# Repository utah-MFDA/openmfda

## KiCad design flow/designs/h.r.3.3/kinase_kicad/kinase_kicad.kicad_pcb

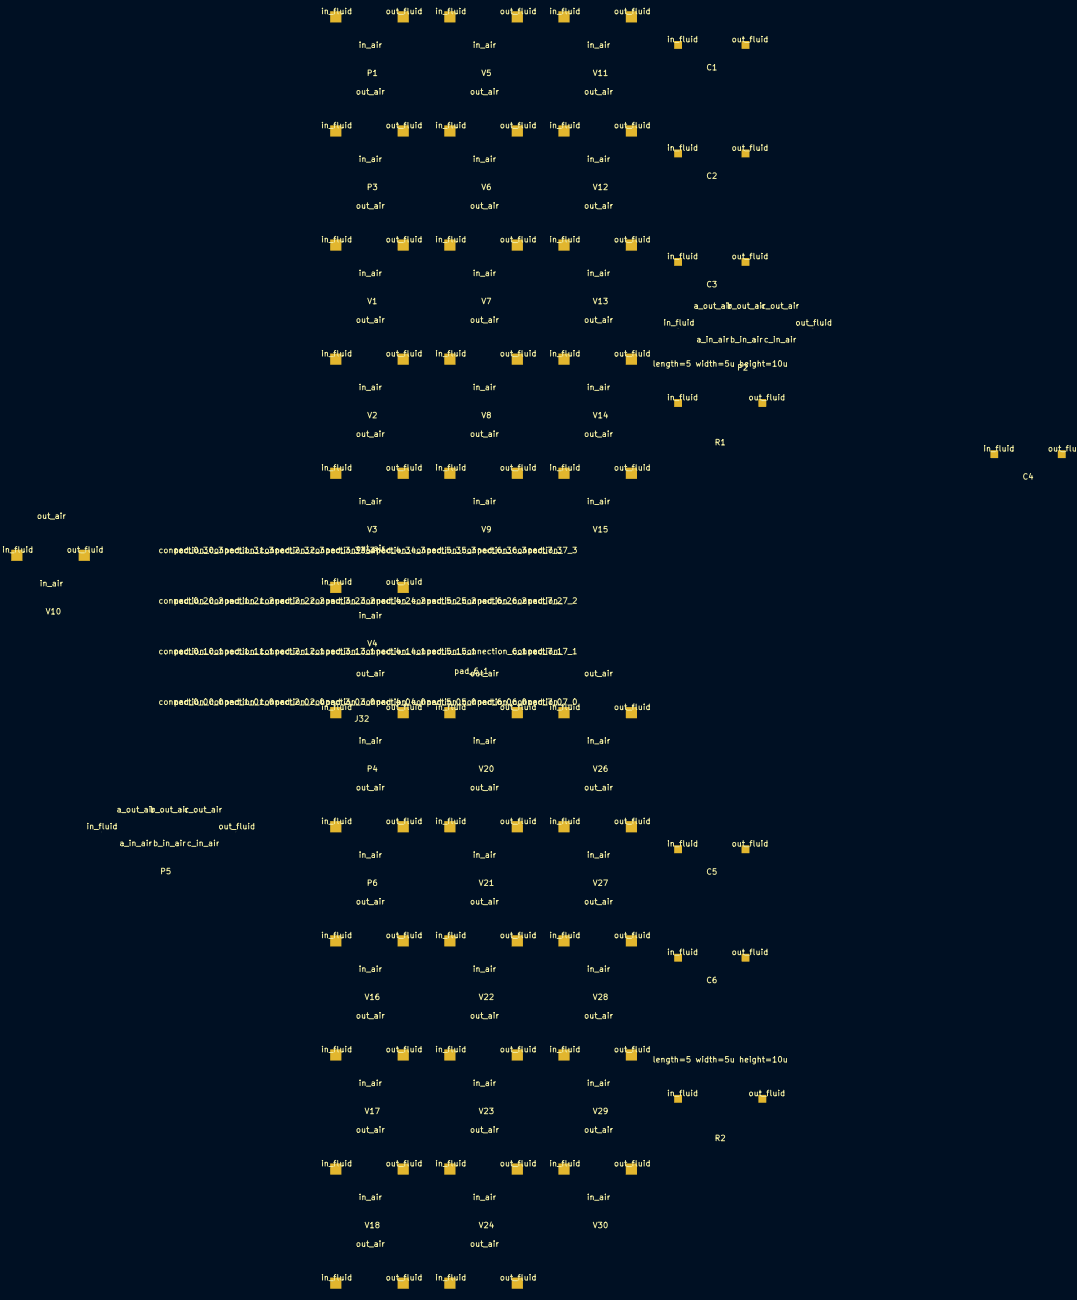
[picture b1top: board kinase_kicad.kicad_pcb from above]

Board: 10 copper layers, 54 parts (0 on the bottom side), 52 nets.

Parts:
C1, C2, C3, C4, C5, C6: serpentine_100px_0
J1, J2, J3, J4, J27, J28, J29, J30, J31: pinhole_325px_0
J32: interconnect_8x4
P1, P3, P4, P6: valve_80px_1
P2, P5: pump_40px_0
R1, R2: length=5 width=5u height=10u; inline_res_40nl
V1, V2, V3, V4, V5, V6, V7, V8, V9, V10, V11, V12, V13, V14, V15, V16, V17, V18, V19, V20, V21, V22, V23, V24, V25, V26, V27, V28, V29, V30: valve_80px_1

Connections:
/component1/fluid_in3: J4.1 (connect_1), V22.3 (c)
/component1/out: J31.1 (connect_1), V30.2 (fluid_right)
/component/control.circulate1: J32.14, V4.3 (control_in)
/component/control.circulate2: J32.10, V2.3 (control_in)
/component/control.circulate3: J32.11, V3.3 (control_in)
/component/control.circulate_in: J32.9, V1.3 (control_in)
/component/control.circulate_out: J32.16, V5.3 (control_in)
/component/control.filter1: J32.12, V8.3 (control)
/component/control.filter2: J32.13, V9.3 (control)
/component/control.filter3: J32.24, V11.3 (control)
/component/control.filter4: J32.23, V10.3 (control)
/component/control.flush1: J32.15, V6.3 (control_in)
/component/control.flush2: J32.17, V12.3 (control_in)
/component/control.flush3: J32.19, V14.3 (control_in)
/component/control.out: J32.22, V15.3 (control_in)
/component/control.stage: J32.18, V13.3 (control_in)
/component/fluid_in1: J1.1 (connect_1), V7.1 (a), V22.1 (a)
/component/fluid_in2: J2.1 (connect_1), V7.2 (b), V22.2 (b)
/component/fluid_in3: J3.1 (connect_1), V7.3 (c)
/component/flush_1: J28.1 (connect_1), V6.2 (fluid_right), V21.2 (fluid_right)
/component/flush_2: J29.1 (connect_1), V12.2 (fluid_right), V27.2 (fluid_right)
/component/flush_3: J30.1 (connect_1), V14.1 (fluid_left), V29.1 (fluid_left)
/component/out: J27.1 (connect_1), V15.2 (fluid_right)
/component/pump1: J32.1, P2.3 (pump_1)
/component/pump2: J32.2, P2.5 (pump_2)
/component/pump3: J32.3, P2.7 (pump_3)
/pump_flush_lh_1: P2.4 (pump_1f), P5.3 (pump_1)
/pump_flush_lh_2: P2.6 (pump_2fl), P5.5 (pump_2)
unnamed: C1.1 (in_1), V2.1 (fluid_left)
unnamed: C2.1 (in_1), V4.1 (fluid_left), V6.1 (fluid_left)
unnamed: C3.1 (in_1), V11.2 (fluid_out)
unnamed: C4.1 (in_1), V17.1 (fluid_left)
unnamed: C5.1 (in_1), V19.1 (fluid_left), V21.1 (fluid_left)
unnamed: C6.1 (in_1), V26.2 (fluid_out)
unnamed: P1.1 (in), V8.2 (fluid_out)
unnamed: P3.1 (in), R1.1 (in_1)
unnamed: P3.2 (out), V9.1 (fluid_in)
unnamed: P4.1 (in), V23.2 (fluid_out)
unnamed: P6.1 (in), R2.1 (in_1)
unnamed: P6.2 (out), V24.1 (fluid_in)
unnamed: V1.1 (fluid_left), V2.2 (fluid_right), V3.1 (fluid_left)
unnamed: V3.2 (fluid_right), V8.1 (fluid_in)
unnamed: V4.2 (fluid_right), V5.2 (fluid_right), V9.2 (fluid_out)
unnamed: V10.2 (fluid_out), V13.2 (fluid_right)
unnamed: V11.1 (fluid_in), V14.2 (fluid_right), V15.1 (fluid_left)
unnamed: V5.1 (fluid_left), V12.1 (fluid_left), V13.1 (fluid_left)
unnamed: V16.1 (fluid_left), V17.2 (fluid_right), V18.1 (fluid_left)
unnamed: V18.2 (fluid_right), V23.1 (fluid_in)
unnamed: V19.2 (fluid_right), V20.2 (fluid_right), V24.2 (fluid_out)
unnamed: V20.1 (fluid_left), V27.1 (fluid_left), V28.1 (fluid_left)
unnamed: V25.2 (fluid_out), V28.2 (fluid_right)
unnamed: V26.1 (fluid_in), V29.2 (fluid_right), V30.1 (fluid_left)

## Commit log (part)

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2023-12-05 Add dockerfile.
2023-12-06 Update docker file to use ubuntu
2023-12-11 Fixes to dockerfile, tcl and python scripts to get running with docker.
2023-12-12 Demo now working with latest openroad.
2023-12-12 Other circuits now working with output paths.
2023-12-12 Switch dockerfile to packaged binaries instead of building openroad.
2023-12-14 Explicitly install make, it got removed with the other build tools.
2024-01-09 This is a migration of Brady's xyce_docker_server
    commit number b346b21ca2b601acd6e4e32b09d4d678ca28d0ac into utah-MFDA
2024-01-22 Some tweaks to footprints and jupiter notebook
2024-02-15 Update makefile to have file targets, with updated readme instructions.
2024-02-15 Fix dimension errors in lef files.
2024-02-15 Commit demo configuration script, and add its outputs to the gitignore.
2024-02-23 Initial migration of mfda_30px to pdk repository.
2024-02-23 Renames lef file to have a suffix,. OpenROAD apparently wants lef and tlef files to have distinct names when loaded.
2024-03-20 SCAD flow - Move DEF parsing to new class
2024-04-27 WIP refactor scad_pnr.py parsing
2024-04-27 WIP simulation flow make targets
2024-04-27 Add benchmarks and a minimal synthesis script.
2024-05-05 All benchmarks for ICCAD run up to at least scad
2024-05-05 Update generator script to handle more pins and symlink
2024-05-05 Change options for global placement. Max routing layer should be met8, nesterov place was crashing so is skipped, things are marked inout to fix double drive
2024-05-05 Fix copied benchmarks to be symlinks.
2024-05-05 Rename synth output in openroad.
2024-05-05 Add extra cells to hr33 common.
2024-05-05 Fix IO constraints for several benchmarks
2024-05-05 Ignore openroad version report
2024-05-05 Make a top level synth target
2024-05-17 Fix conflicting names in synthetic benchmarks
2024-05-31 Migrate everything into the openroad makefile.
2024-05-31 Refactor scad component to use opendb
2024-05-31 Remove eval call for component addition.
2024-05-31 Move all scad global config values into a container.
2024-05-31 Refactor to remove eval and consolidate duplicate expressions prior to replacement with opendb.
2024-06-03 Massive refactor of scad flow to switch to opendb.
2024-06-05 Remove extraneous verilog file.
2024-06-05 Add synthesis cleanup and all files for render cleanup.
2024-06-05 Correct the parameter for initialize_floorplan to sites.
2024-06-05 Fix scad dimm calculations
2024-06-05 Fix double overwrite of the scad files during routing file copy.
2024-06-05 Fix warning coming from routing scad library during rendering
2024-06-05 Handle the default point extension case in scad render
2024-06-05 Update benchmarks to VLSISOC submit set
2024-06-06 Remove redundancy in makefile and design configuration.
2024-06-06 Move scad rendering into tools and pdk into platforms directory.
2024-06-06 Move openroad_flow into flow to simplify path
2024-06-06 Bump pillow from 10.2.0 to 10.3.0
    Bumps [pillow](https://github.com/python-pillow/Pillow) from 10.2.0 to 10.3.0.
    - [Release notes](https://github.com/python-pillow/Pillow/releases)
    - [Changelog](https://github.com/python-pillow/Pillow/blob/main/CHANGES.rst)
    - [Commits](https://github.com/python-pillow/Pillow/compare/10.2.0...10.3.0)
    ---
    updated-dependencies:
2024-06-10 Add simulation tool
2024-06-10 Initial kicad network parsing
2024-06-11 Add length csv to simulation recipe
2024-06-11 Latest fixes to HR33 pdk
2024-06-13 Complete flow working with simulation and library building
2024-06-13 Basic kicad schematic netlist extraction.
2024-06-18 Initial conversion script from DEF to kicad board.
2024-08-07 major simulation changes, dimm_file ref fixes, openmfda_flow.py changes
2024-08-27 Move opendb iterator to a module.
2024-08-28 WX exploration
2024-09-12 Create script to generate kicad footprint library from LEF files.
2024-09-12 Remove debugging and local configuration from lef_to_footprint.
2024-09-12 Remove local test config for main in def_to_pcbnew and def_to_board
2024-09-20 Add scripts to generate a platform with different number of metal layers.
2024-09-26 init pkg on main branch
2024-10-17 various tool fixes, scad_gen
2024-10-22 Fix argparse in kicad def scripts
2024-10-24 Fix argparse for consistency in kicad scripts
2024-10-24 Add text labels to kicad footprint export script.
2024-10-24 Formatting text for kicad footprint generator.
2024-10-25 Adjustment for pcell generation, added scad extra includes
2024-10-25 Cleaning and fixed hard coded definitions
2024-10-26 merged with fixed version of generator render
2024-11-01 update to submodules
2024-11-01 py src changes and updates to PCell definitions
2024-11-01 updated pcell_gen commits
2024-11-04 changes to pcell config.mk
2024-11-04 simulation fixes
2024-11-05 Added PCELL as dep to floorplan
2024-11-20 Remove missing submodule in tools/simulation
2024-11-20 Use correct layer height variable in slicer configuration.
2024-12-05 Update h.r.3.3 PDK with kicad symbols and new pad lef file.
2024-12-05 Setup kinase_activity 2 variant to use explicitly placed chambers and pads.
2024-12-05 Add KiCAD examples for kinase and mnacidpro
2024-12-10 Update submodules to fix broken inner modules.
2025-01-13 WIP plugin config write out
2025-01-17 Kinase example macro and pad placement using latest openroad commands.
2025-01-21 WIP export happy: :
2025-01-22 WIP PNR working.
2025-01-23 updates to render gen v2 and helper scripts
2025-01-31 Refactor WIP
2025-01-31 Add xvfb command variable.
2025-01-31 Convert between Y-axis orientation between kicad and def.
2025-01-31 Create kicad layer names and vias use correct ids.
2025-02-03 extra render and routing scripts
2025-02-03 devel changes for main flow
2025-02-03 now tracks a stable branch
2025-02-03 def load and export functions, changes to iteration implementation
2025-02-04 Write locked Kicad footprints as explicit placed macro.
2025-02-04 Remove hard coded flow path.
2025-02-06 Fix orientation in the lef to kicad footprint conversion script.
2025-02-10 Update h.r.3.3 to pdk 0.0.2 beta
2025-02-10 Update kinase_activity_2 to use new openroad syntax and switch from bump pad to pin. Bump pads generate but special nets are not routed.
2025-02-28 rm unneeded xyce flow, moved to simulation
2025-03-15 addition to tcl scripts, fixes to py code
2025-04-14 Lots of clean up, more examples. Added Docker implementation
2025-04-17 write out def
2025-04-18 Added make script
2025-04-18 Makefile merge fixes
2025-04-24 Fix to pcell gen
2025-04-30 Fixes to route fixes and SCAD_LIB ref
2025-05-06 fixes to silent, small mk file chg, src mnt docker
2025-05-08 Parse verilog models
2025-05-23 DEF_FIX changes
2025-05-27 def graph generation, support to submods in verilog
2025-06-04 grt script fix with added pin and routing size def to scad
2025-06-04 fixed routing size arg
2025-06-17 fix simulation branch ref and gitmodules reference
2025-06-17 Fixed Makefile ref for simulation
2025-06-17 updated component file
2025-06-21 fixes to smartt
2025-06-22 update pdk ref, lib link fix, test script fix
2025-06-23 src reference and scad fix
2025-06-26 fixes to req and update docs
2025-07-02 WIP Kinase pad upggrade
2025-07-03 WIP fixing sizes
2025-07-03 WIP fix pins
2025-07-24 Add citation.cff
2025-07-29 Added documentation for the flow pdk
2025-07-29 Change tracked pdk to lib 0.0.2
2025-07-29 no tracking of lock files
2025-07-30 Moved 3D printer definitions to sperate file, config_3dp.mk
2025-08-04 Added platform template
2025-08-28 Cleanup WIP
2025-08-28 Update benchmarks and PDK
2025-08-28 Initial ILP 3d formulation.
2025-09-03 add comments makefile and config name and link
2025-09-03 update to run_mfda_docker
2025-09-05 Attempt at a frontier exploring shell placement
2025-09-06 3D routing success on small test graph
2025-09-08 WIP, works for half of the graph.
2025-09-10 Working version with relaxed constraints.
2025-09-24 Update json graph extraction to pull metadata
2025-09-24 Update frontier tracking with multiple styles
2025-09-24 Remove some extraneous kinase benchmark files.
2025-09-27 Working version of fluid first placement
2025-09-29 Migrate network type checks to the helper module.
2025-09-29 Working hypergraph reader
2025-09-29 Consolidate naming to cylinder
2025-09-29 Fixed whatever was failing
2025-09-30 Establish hard upper and lower bounds for each scenario
2025-09-30 Fix direction of numeric check
2025-09-30 Fix broken assertion about shell assignment
2025-10-02 Add an experiment in a complete single pass solve
2025-10-02 Add in another slice implementation that uses both forward and backward lookahead
2025-10-02 Conslidate the slice bound functions to generalized
2025-10-06 Refactor to add argparse
2025-10-07 Remove committed scad files.
2025-10-07 Switch to argeparse flags in makefile
2025-10-07 Add correct orientation bounds to the bounding max/min
2025-10-07 Remove redundant horizontal version of bounding
2025-10-07 Set timeout to the actual argument
2025-10-08 Fix argument order for bounding function
2025-10-09 Do direct constraint between components rather than trying the bounding variable.
2025-10-09 Add option to skip non-flow nodes
2025-10-10 Add option to collapse non-hyperedges
2025-10-10 Add missing edge properties
2025-10-10 Implement peer relationships and add a switch to do minimization of relaxation
2025-10-10 add some attachment constraints which would enforce a non-crossing hexagonal connection scheme.
2025-10-10 Add a runner which backtracks. Doesn't really work.
2025-10-15 new lighter slicer implementation
2025-10-15 Makefile files post merge
2025-10-15 update lef links and add scad to Makefile
2025-10-15 SCAD_LIB in Makefile, fixes to re-iter
2025-10-15 modified kicad files
2025-10-16 cleaned up interfaces, build-all added
2025-10-16 add SITES to h.r.3.3_0.0.2.tlef
2025-10-16 update pdk
2025-10-20 rm git added lines
2025-10-21 Fixes for kicad
2025-10-22 Add dimensional reduction script prototype.
2025-10-23 Add freeze of 3d route requirements file.
2025-10-23 Checking what PCA does out of the box.
2025-10-23 Add some vars to makefile,
2025-10-25 Initial kicad server plugins
2025-10-27 WIP on server testing
2025-10-27 Update simulation repo
2025-10-28 Update simulation submodule
2025-10-28 Remove bad opendb library
2025-10-28 Remove broken relative import
2025-10-28 Update example pcb
2025-10-28 Server plugin implementation
2025-10-28 Fix configuration generation
2025-10-28 Plugin layout cleanup
2025-10-28 Fix typos
2025-10-28 Sort of working plugin, crashes on copying the data in occasionally.
2025-10-28 Really good results from existing dimensional reduction algorithms
2025-10-29 update to pdk
2025-10-29 Dev-kcad fixes, edits to scripts for new flow and rm padring for now
2025-10-31 Fix footprint id access in kicad server, v9 changes footprint id to a separate method rather than field.
2025-10-31 Fix pathing issues in kicad server
2025-11-01 Move kicad-dev over kicad to prepare for merge
2025-11-11 Make rendering more generic with color selection
2025-11-11 Add some benchmark results
2025-11-11 Handle multigraph in networkx helpers
2025-11-11 Set bounding back to distance minimization
2025-11-11 Cleanup and optiomize dimension reduction
2025-11-11 Add constraints separate from solving
2025-11-12 Update benchmarks with parameterized versions
2025-11-12 Update benchmarks for 3d routing
2025-11-12 Comment out the peer bounding
2025-11-13 Configurable log file
2025-11-13 Strip out constraint and variable names causing conflicts
2025-11-13 Add an all at once horizontal mode
2025-11-13 Add benchmark results
2025-11-13 Update kinase benchmark
2025-11-13 Add pad versions of mnacidpro and mrnaiso
2025-11-16 Store the direction and highwater information for retry
2025-11-16 Update results"
2025-11-16 Change some settings in makefile.
2025-11-16 Call out to subprocess to run scip to try and avoid memory issues
2025-11-16 Extract stats and log during solve
2025-12-02 Data from DAC submission
2025-12-02 Cleanup dimension runs
2025-12-05 Add intersection helper
2025-12-05 Add in rendering with pyvista
2026-02-27 fixes to scad render graph build
2026-03-23 fixes to pin detection
2026-03-25 Fixed graph building, needs more updates
2026-04-03 include def_load in scad render
2026-04-03 Allows for rendering of specific def through make
